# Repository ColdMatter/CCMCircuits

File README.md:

CCMCircuits
===========

This is a repository for circuits used by the Centre for Cold Matter at Imperial College. Each project should be in its own directory, and should contain a .brd and a .sch file, a "readme.md" file which gives any useful information on the circuit. You can also upload files used to make the circuit in the PCB mill, and any measurements that you make of the circuit's behaviour. Please try not to upload all of the temporary files made by Eagle.

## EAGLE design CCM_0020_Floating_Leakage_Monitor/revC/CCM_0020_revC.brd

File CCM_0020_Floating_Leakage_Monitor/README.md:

# CCM_0020 50kV Floating pA Leakage Current Monitor
     
This is a circuit used to monitor pA-level leakage currents on the HV plates of 
the ultracold edm experiment.  We have a design goal of having the leakage currents be less than 25 pA.  To make sure this is the case, we want to be able to measure currents at the pA level.  This is hard.  Floating the entire circuit up to a few tens of kV makes it even harder.  This is my kind of problem -NF.    

## Design Resources
- Bob Pease: What's all this teflon stuff anyhow?
- Bob Pease: What's all this femtoampere stuff anyhow?
- Keithley low-level measurement handbook
- LM662 datasheet
- Analog Devices ADA4530-1 datasheet: https://www.analog.com/media/en/technical-documentation/data-sheets/ADA4530-1.pdf 
- Analog Devices ADA4530-1 demo board user's guide: https://www.analog.com/media/en/technical-documentation/user-guides/ADA4530-1R-EBZ_UG-865.pdf

## Design Notes
The transmitter section of the circuit features three critical design elements: 
ultra low input leakage currents, ultra low power consumption, and high voltage 
isolation.  The former is required of any circuit capable of measuring currents 
on the pA level.  The most sensitive way to measure extremely low currents (like the fA-level features by some of the op amps we'll be using here) is to integrate for many seconds and read off the voltage.  Of course, you need an integrating capacitor with low leakage too: a length of teflon coated coaxial wire is a good choice, you can even drive the coax outer conductor with a shielding potential ("self shielded") to avoid dielectric relaxation effects.  The small enclosed volume also lowers the sensitivity to cosmic rays, to which you are sensitive to at this level.  To monitor the leakage on the edm electric field plates, we need a time-resolved signal, so integrating is out.  We don't care at the fA level, so this shouldn't pose a problem.  A sense resistor + buffer amplifier (alternatively, a transimpedance amplifier) should be sensitive enough and give us real-time measurements. 

Achieving ultra low input leakage currents starts with choosing an appropriate 
operational amplifier, in this case in a voltage "buffer" configuration.  Luckily, there are a number of (CMOS) op amps on the market that feature input leakage currents on the order of 10 fA.  We have the additional challenge of needing an op amp that has low quiescent current requirements.  The LMP2231 made by Texas Instruments seems to fit the bill: 20 fA input leakage current (typical, 1 pA max) while only needing 10 uA of quiescent current.

Taking advantage of the ultra-low input current leakage specification of our chosen op amp requires a significant amount of layout/design work.  It won't do us any good to use such an op amp on a dirty FR4 board that will leak currents of many pA into our inputs every time the humidity changes.  The first line of defense is to use a low-leakage circuit board material.  A 4-layer board with outer layers made of Rogers 4350B (a ceramic) and the inner substrate made of FR408 (for strength) seems like a good way to go.  Beyond that, high-impedance circuit inputs are shielded at numerous levels.  The buffer op amp inputs use a "guard ring" driven by a low impedance source (the op amp output) held at the same voltage as the inputs themselves, which eliminates leakage from surrounding on-board potentials.  The guard ring is exposed copper so that no charge carriers can leak past on the soldermask or silkscreen layers.  The guard ring extends underneath the top ceramic layer to shield the input pins (from below) from the FR4 inner layer.  A via fence on the outer perimeter of the guard ring completes the board-level shielding.  Additional shielding is achieved by two layers of brass boxes, the inner one (top and bottom of the board) at the same potential as the guard ring and the outer one (again, on both top and bottom) at floating "ground".  A triax cable uses the same two shielding potentials to bring the HV line into the circuit.

Of all the challenges to overcome here, the HV isolation is perhaps the easiest to overcome.  Optek makes the OPI15X series of opto-couplers/isolators that are rated to 50 kV in air.  We could just do our usual trick: use a sense resistor and buffer amplifier to generate a voltage, convert that voltage to a frequency using a VtoF converter and optically transmit that frequency.  Optical transmission can either be done using a fiber (e.g. Agilent's HFBR-1520) or an Optek OPI155 optoisolator.  However, both of these require significant (many mA) led drive current in order to toggle the logic output on the receiver.  Instead, I'm planning to use the OPI150 optocoupler (transmitting LED + receiving phototransistor) with the phototransistor receiver wired as a photodiode (base shorted to emitter) and the generated photocurrent being detected by a high-gain transimpedance amplifier.  In principle, this should allow us to get the signal out using much less power.  The output of the transimpedance could even feed into a precisely tuned comparator to give high sensitivity and logic-level outputs.  We could even transmit an analog signal instead of a digital one using the same setup but without the receiver comparator.  I think the digital approach will have better noise immunity, larger dynamic range, and potentially uses less power.  That means we'll likely have to do VtoF after all.  Even though you can't buy low power VtoF ICs (or VCOs), you can build your own.  The LTC1541 [op amp + comparator + voltage reference] has one option in the applications section of its datasheet.  You can build a 0-10 kHz VtoF with quiescent current requirements around 5 uA, some 200 x less than the lowest power monolithic solution.  

Along with the problem of high-voltage isolation comes the question of how to power the isolated transmitter section of the circuit.  The most obvious answer is to use batteries, but in practice that turns out to be relatively annoying.  An alternative is to power the circuit using some high-power leds and a solar panel on the transmitter.  This sounds elegant, and I think it probably could be if the transmitter was designed for very low-power operation, but in practice it makes the current monitors very big (and bright -- you need lots of optical power).  I've decided to try something crazy: design for ultra-low power on the transmitter and power it via photocurrent generated from (many of)
the same model of optocoupler that we're using to get the signal out.  With a max allowed LED current of 50 mA and a transfer ratio of ~2000:1, with six optocouplers I think I should be able to create a 2.5 V, 50 uA power supply on the transmitter circuit.  With a careful design I think that should be enough. 

## Known Issues

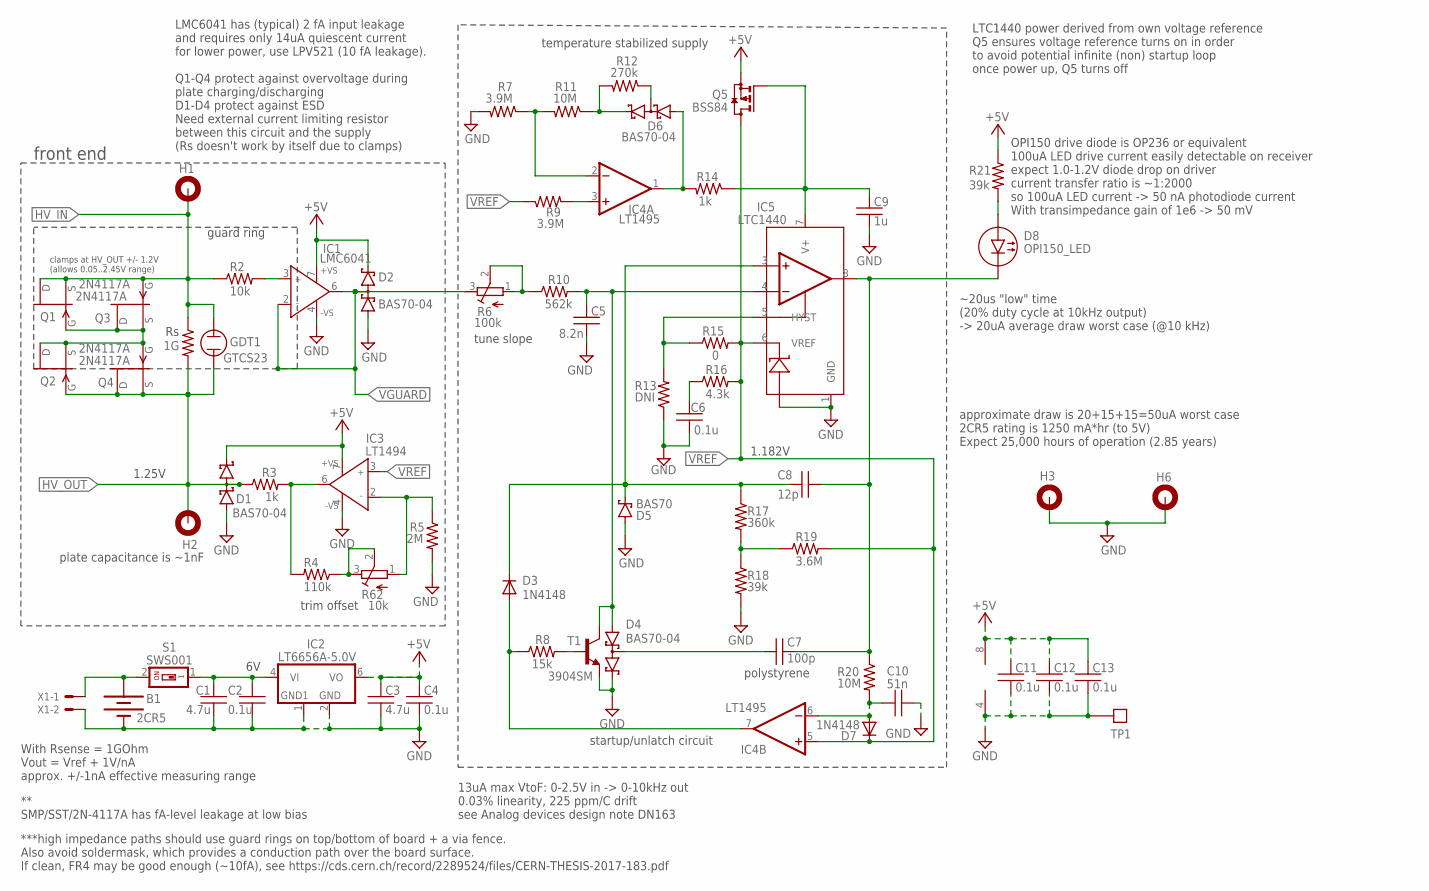
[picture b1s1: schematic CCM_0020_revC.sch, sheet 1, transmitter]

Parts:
B1: 2CR5
C1, C3: 4.7u; 0603
C2, C4, C6, C11, C12, C13: 0.1u; 0603
C5: 8.2n; 0603
C7: 100p; 0603
C8: 12p; 0603
C9: 1u; 0603
C10: 51n; 0603
D1, D2, D4, D6: BAS70-04; SOT23
D3, D7: 1N4148; SOD323_ST
D5: BAS70; SOD323_ST
D8: OPI150_LED
GDT1: GTCS23
H1, H2, H3, H6: MOUNT-PAD-ROUND3.0; 3,0-PAD
IC1: LMC6041; SO8
IC2: LT6656A-5.0V; SOT23-6
IC3: LT1494; SO8
IC4: LT1495; SO8
IC5: LTC1440; SO8
Q1, Q2, Q3, Q4: 2N4117A; SOT23
Q5: BSS84; SOT23
R1: 1G; 2512
R2: 10k; 0603
R3, R14: 1k; 0603
R4: 110k; 0603
R5: 2M; 0603
R6: 100k; RTRIM3224W
R7, R9: 3.9M; 0603
R8: 15k; 0603
R10: 562k; 0603
R11, R20: 10M; 0603
R12: 270k; 0603
R13: DNI; 0603
R15: 0; 0603
R16: 4.3k; 0603
R17: 360k; 0603
R18, R21: 39k; 0603
R19: 3.6M; 0603
R62: 10k; RTRIM3224W
S1: SWS001; SMS-001
T1: 3904SM; SOT23
TP1: TESTPOINT
X1: 22-23-2021

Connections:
+5V: C3.1, C4.1, C11.1, C12.1, C13.1, D1.2 (C2), D2.2 (C2), IC1.7 (+VS), IC2.6 (VO), IC3.7 (+VS), IC4.8 (V+), Q5.2 (S), R21.1
GND: B1.V- (-), C1.2, C2.2, C3.2, C4.2, C5.2, C6.1, C9.2, C10.2, C11.2, C12.2, C13.2, D1.1 (A1), D2.1 (A1), D4.2 (C2), D5.A, H3.B3,0, H6.B3,0, IC1.4 (-VS), IC2.1 (GND1), IC2.2 (GND), IC3.4 (-VS), IC4.4 (V-), IC5.1 (GND), IC5.2 (V-), R5.2, R7.2, R13.1, R18.2, T1.2 (E), TP1.P$1, X1.2
HV_IN: GDT1.P$1 (1), H1.B3,0, Q1.1 (D), Q1.2 (S), Q3.3 (G), R1.1, R2.1
HV_IN1: Q1.3 (G), Q2.1 (D), Q2.2 (S), Q3.1 (D), Q3.2 (S), Q4.3 (G)
HV_OUT: D1.3 (C1A2), GDT1.P$2 (2), H2.B3,0, Q2.3 (G), Q4.1 (D), Q4.2 (S), R1.2, R3.1
HYST: IC5.5 (HYST), R13.2, R15.1
unnamed: C9.1, IC5.7 (V+), Q5.1 (G), R14.1
unnamed: D8.P$1 (1(A)), R21.2
unnamed: R6.1 (A), R6.2 (S), R10.1
unnamed: IC1.3 (IN+), R2.2
unnamed: C6.2, R16.1
unnamed: C5.1, D4.1 (A1), IC5.4 (-IN), R10.2, T1.3 (C)
unnamed: C7.1, D4.3 (C1A2)
unnamed: R8.2, T1.1 (B)
unnamed: D3.A, IC4.7 (OUT), R8.1
unnamed: R17.2, R18.1, R19.1
unnamed: C8.1, D3.C, D5.C, IC5.3 (+IN), R17.1
unnamed: C10.1, D7.A, IC4.6 (-IN), R20.2
unnamed: D6.1 (A1), IC4.1 (OUT), R14.2
unnamed: D6.2 (C2), R11.1, R12.2
unnamed: IC4.2 (-IN), R7.1, R11.2
unnamed: C1.1, C2.1, IC2.4 (VI), S1.1
unnamed: D6.3 (C1A2), R12.1
unnamed: IC4.3 (+IN), R9.2
unnamed: IC3.2 (IN-), R5.1, R62.1 (A)
unnamed: IC3.6 (OUT), R3.2, R4.2
unnamed: R4.1, R62.2 (S), R62.3 (E)
unnamed: B1.V+ (+), S1.2, X1.1
VGUARD: D2.3 (C1A2), IC1.2 (IN-), IC1.6 (OUT), R6.3 (E)
VREF: D7.C, IC3.3 (IN+), IC4.5 (+IN), IC5.6 (VREF), Q5.3 (D), R9.1, R15.2, R16.2, R19.2
VTOF_OUTPUT: C7.2, C8.2, D8.P$2 (2(C)), IC5.8 (OUT), R20.1

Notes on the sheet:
** SMP/SST/2N-4117A has fA-level leakage at low bias
plate capacitance is ~1nF
With Rsense = 1GOhm Vout = Vref + 1V/nA approx. +/-1nA effective measuring range
***high impedance paths should use guard rings on top/bottom of board + a via fence. Also avoid soldermask, which provides a conduction path over the board surface. If clean, FR4 may be good enough (~10fA), see https://cds.cern.ch/record/2289524/files/CERN-THESIS-2017-183.pdf
polystyrene
front end
13uA max VtoF: 0-2.5V in -> 0-10kHz out 0.03% linearity, 225 ppm/C drift see Analog devices design note DN163
1.182V
clamps at HV_OUT +/- 1.2V (allows 0.05..2.45V range)
approximate draw is 20+15+15=50uA worst case 2CR5 rating is 1250 mA*hr (to 5V) Expect 25,000 hours of operation (2.85 years)
guard ring
~20us "low" time (20% duty cycle at 10kHz output) -> 20uA average draw worst case (@10 kHz)
OPI150 drive diode is OP236 or equivalent 100uA LED drive current easily detectable on receiver expect 1.0-1.2V diode drop on driver current transfer ratio is ~1:2000 so 100uA LED current -> 50 nA photodiode current With transimpedance gain of 1e6 -> 50 mV
LMC6041 has (typical) 2 fA input leakage and requires only 14uA quiescent current for lower power, use LPV521 (10 fA leakage). Q1-Q4 protect against overvoltage during plate charging/discharging D1-D4 protect against ESD Need external current limiting resistor between this circuit and the supply (R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
temperature stabilized supply
startup/unlatch circuit
tune slope
1.25V
LTC1440 power derived from own voltage reference Q5 ensures voltage reference turns on in order to avoid potential infinite (non) startup loop once power up, Q5 turns off
trim offset

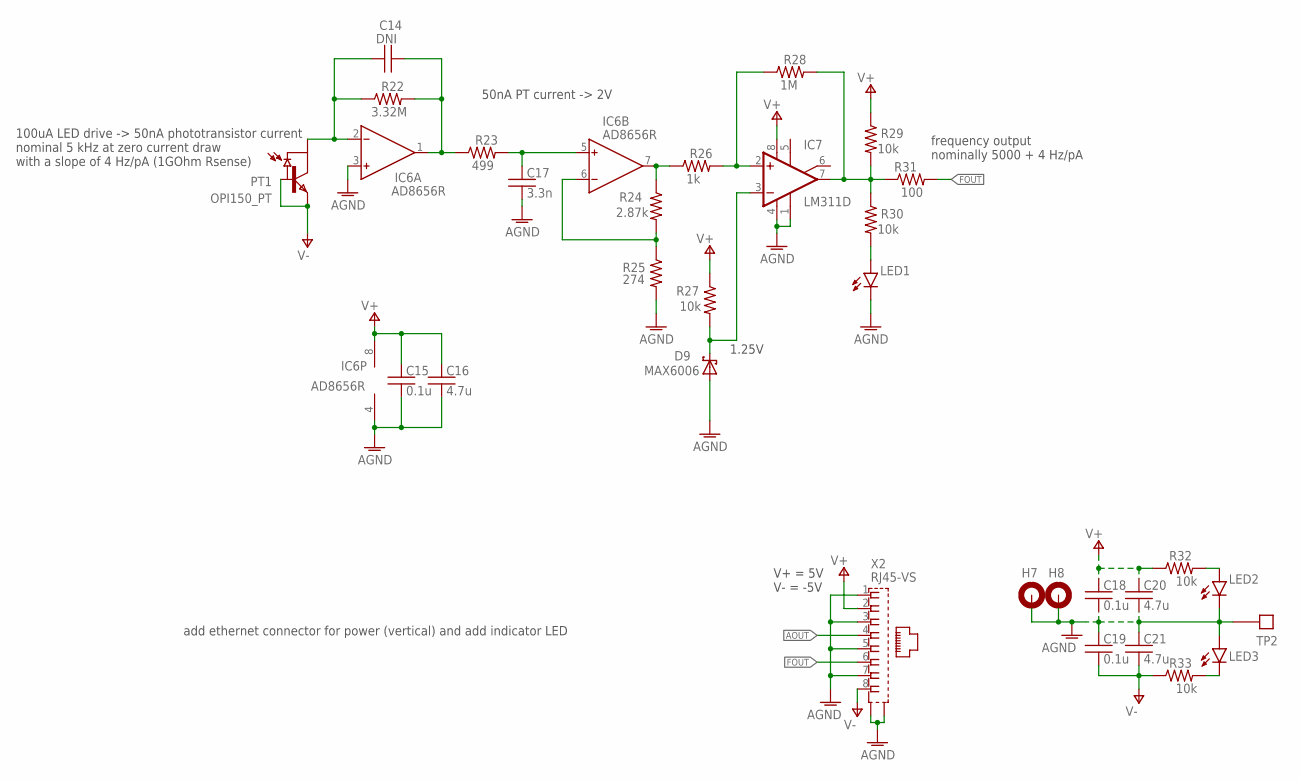
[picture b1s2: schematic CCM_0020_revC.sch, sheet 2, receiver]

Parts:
C14: DNI; 0603
C15, C18, C19: 0.1u; 0603
C16, C20, C21: 4.7u; 0603
C17: 3.3n; 0603
D9: MAX6006; SOT23
H7, H8: MOUNT-PAD-ROUND3.0; 3,0-PAD
IC6: AD8656R; SO8
IC7: LM311D; SO08
LED1, LED2, LED3: LEDCHIP-LED0603; CHIP-LED0603
PT1: OPI150_PT; OPI150_PHOTOTRANSISTOR
R22: 3.32M; 0603
R23: 499; 0603
R24: 2.87k; 0603
R25: 274; 0603
R26: 1k; 0603
R27, R29, R30, R32, R33: 10k; 0603
R28: 1M; 0603
R31: 100; 0603
TP2: TESTPOINT
X2: RJ45-VS

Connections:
AGND: C15.2, C16.2, C17.2, C18.2, C19.1, C20.2, C21.1, D9.2 (A), H7.B3,0, H8.B3,0, IC6.3 (IN+), IC6.4 (V-), IC7.1 (GND), IC7.4 (V-), LED1.C, LED2.C, LED3.A, R25.2, TP2.P$1, X2.1, X2.3, X2.5, X2.7, X2.S1, X2.S2; also elsewhere on the board
AOUT: X2.4; also elsewhere on the board
FOUT: R31.2, X2.6; also elsewhere on the board
unnamed: LED2.A, R32.2
unnamed: C14.1, IC6.2 (IN-), PT1.P3 (COLLECTOR), R22.1
unnamed: C14.2, IC6.1 (OUT), R22.2, R23.1
unnamed: C17.1, IC6.5 (IN+), R23.2
unnamed: IC6.6 (IN-), R24.2, R25.1
unnamed: IC6.7 (OUT), R24.1, R26.1
unnamed: IC7.2 (+IN), R26.2, R28.1
unnamed: D9.1 (C), IC7.3 (-IN), R27.2
unnamed: LED3.C, R33.2
unnamed: LED1.A, R30.2
unnamed: IC7.7 (OUT), R28.2, R29.2, R30.1, R31.1
V+: C15.1, C16.1, C18.1, C20.1, IC6.8 (V+), IC7.8 (V+), R27.1, R29.1, R32.1, X2.2; also elsewhere on the board
V-: C19.2, C21.2, PT1.P4 (BASE), PT1.P5 (EMITTER), R33.1, X2.8; also elsewhere on the board

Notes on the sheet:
100uA LED drive -> 50nA phototransistor current nominal 5 kHz at zero current draw with a slope of 4 Hz/pA (1GOhm Rsense)
50nA PT current -> 2V
1.25V
frequency output nominally 5000 + 4 Hz/pA
V+ = 5V V- = -5V
add ethernet connector for power (vertical) and add indicator LED

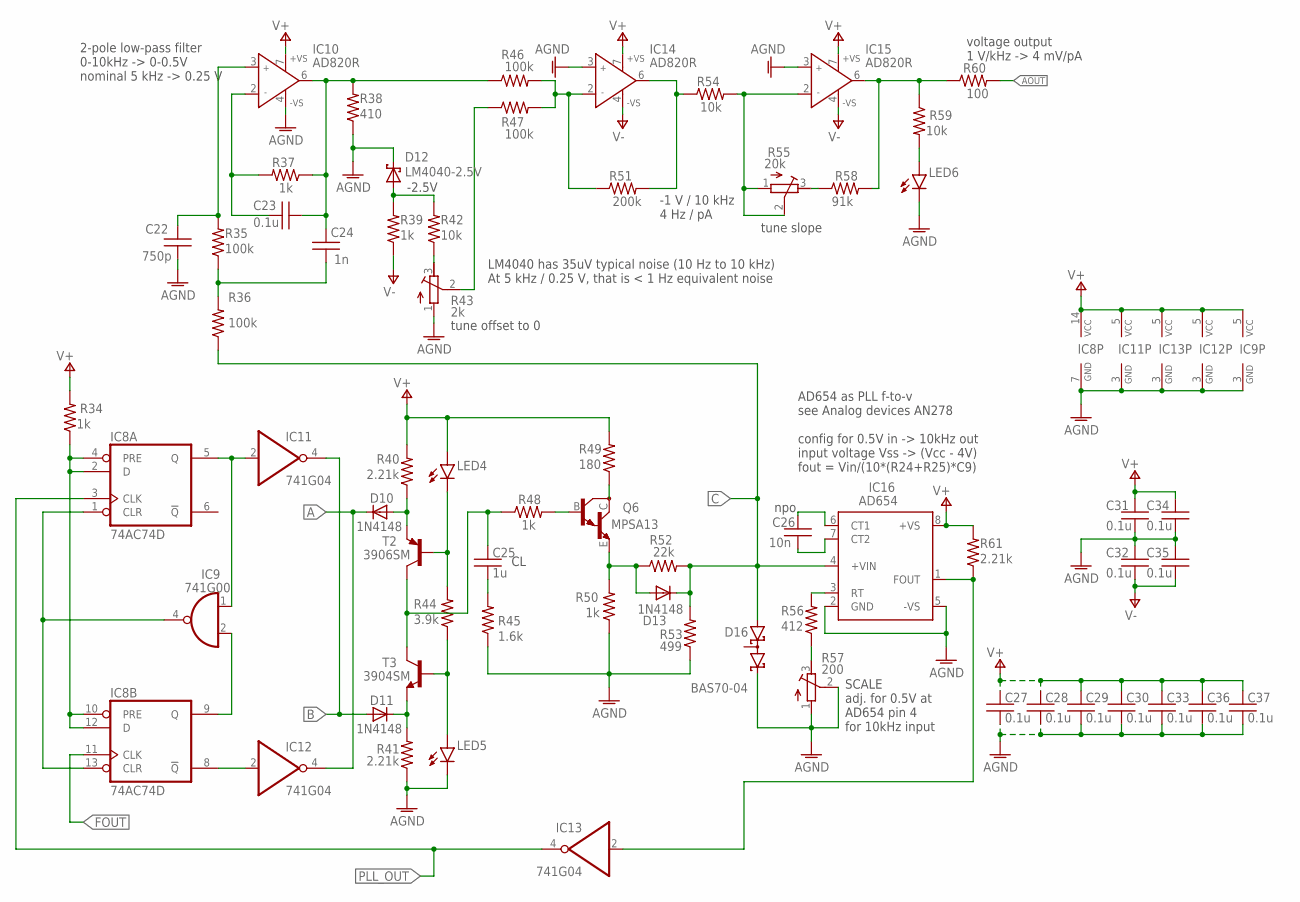
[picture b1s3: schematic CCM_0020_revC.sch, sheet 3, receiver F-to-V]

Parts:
C22: 750p; 0603
C23, C27, C28, C29, C30, C31, C32, C33, C34, C35, C36, C37: 0.1u; 0603
C24: 1n; 0603
C25: 1u; 0603
C26: 10n; 0603
D10, D11, D13: 1N4148; SOD323_ST
D12: LM4040-2.5V; SOT23
D16: BAS70-04; SOT23
IC8: 74AC74D; SO14
IC9: 741G00; SOT23-5
IC10, IC14, IC15: AD820R; SO8
IC11, IC12, IC13: 741G04; SOT23-5
IC16: AD654; SO08
LED4, LED5, LED6: LEDCHIP-LED0603; CHIP-LED0603
Q6: MPSA13; SOT23-BEC
R34, R37, R39, R48, R50: 1k; 0603
R35, R36, R46, R47: 100k; 0603
R38: 410; 0603
R40, R41, R61: 2.21k; 0603
R42, R54, R59: 10k; 0603
R43: 2k; RTRIM3224W
R44: 3.9k; 0603
R45: 1.6k; 0603
R49: 180; 0603
R51: 200k; 0603
R52: 22k; 0603
R53: 499; 0603
R55: 20k; RTRIM3224W
R56: 412; 0603
R57: 200; RTRIM3224W
R58: 91k; 0603
R60: 100; 0603
T2: 3906SM; SOT23-BEC
T3: 3904SM; SOT23

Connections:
A: D10.C, IC12.4 (O)
AGND: C22.1, C27.2, C28.2, C29.2, C30.2, C31.1, C32.2, C33.2, C34.1, C35.2, C36.2, C37.2, D12.1 (C), D16.2 (C2), IC8.7 (GND), IC9.3 (GND), IC10.4 (-VS), IC11.3 (GND), IC12.3 (GND), IC13.3 (GND), IC14.3 (IN+), IC15.3 (IN+), IC16.2 (GND), IC16.5 (-VS), LED5.C, LED6.C, R38.1, R41.1, R43.1 (A), R45.1, R50.1, R53.1, R57.1 (A), R57.2 (S); also elsewhere on the board
AOUT: R60.2; also elsewhere on the board
B: D11.A, IC11.4 (O)
C: D13.C, D16.1 (A1), IC16.4 (+VIN), R36.1, R52.2, R53.2
FOUT: IC8.11 (CLK); also elsewhere on the board
unnamed: IC8.1 (CLR), IC8.13 (CLR), IC9.4 (O)
unnamed: IC8.9 (Q), IC9.2 (I1)
unnamed: IC8.8 (!Q), IC12.2 (I)
unnamed: IC8.5 (Q), IC9.1 (I0), IC11.2 (I)
unnamed: R56.1, R57.3 (E)
unnamed: C25.1, R48.1, T2.C, T3.3 (C)
unnamed: D11.C, R41.2, T3.2 (E)
unnamed: LED4.C, R44.2, T2.B
unnamed: LED5.A, R44.1, T3.1 (B)
unnamed: C25.2, R45.2
unnamed: Q6.C, R49.1
unnamed: Q6.B, R48.2
unnamed: D13.A, Q6.E, R50.2, R52.1
unnamed: IC16.3 (RT), R56.2
unnamed: C26.1, IC16.6 (CT1)
unnamed: C26.2, IC16.7 (CT2)
unnamed: IC13.2 (I), IC16.1 (FOUT), R61.1
unnamed: C24.1, R35.1, R36.2
unnamed: C22.2, IC10.3 (IN+), R35.2
unnamed: C23.2, C24.2, IC10.6 (OUT), R37.1, R38.2, R46.1
unnamed: C23.1, IC10.2 (IN-), R37.2
unnamed: IC14.2 (IN-), R46.2, R47.2, R51.1
unnamed: IC15.2 (IN-), R54.2, R55.1 (A), R55.2 (S)
unnamed: IC15.6 (OUT), R58.2, R59.1, R60.1
unnamed: IC14.6 (OUT), R51.2, R54.1
unnamed: D12.2 (A), R39.2, R42.2
unnamed: R43.2 (S), R47.1
unnamed: R42.1, R43.3 (E)
unnamed: R55.3 (E), R58.1
unnamed: D10.A, R40.1, T2.E
unnamed: LED6.A, R59.2
unnamed: IC8.2 (D), IC8.4 (PRE), IC8.10 (PRE), IC8.12 (D), R34.1
PLL_OUT: IC8.3 (CLK), IC13.4 (O)
V+: C27.1, C28.1, C29.1, C30.1, C31.2, C33.1, C34.2, C36.1, C37.1, IC8.14 (VCC), IC9.5 (VCC), IC10.7 (+VS), IC11.5 (VCC), IC12.5 (VCC), IC13.5 (VCC), IC14.7 (+VS), IC15.7 (+VS), IC16.8 (+VS), LED4.A, R34.2, R40.2, R49.2, R61.2; also elsewhere on the board
V-: C32.1, C35.1, IC14.4 (-VS), IC15.4 (-VS), R39.1; also elsewhere on the board

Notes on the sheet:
npo
SCALE adj. for 0.5V at AD654 pin 4 for 10kHz input
2-pole low-pass filter 0-10kHz -> 0-0.5V nominal 5 kHz -> 0.25 V
AD654 as PLL f-to-v see Analog devices AN278 config for 0.5V in -> 10kHz out input voltage Vss -> (Vcc - 4V) fout = Vin/(10*(R24+R25)*C9)
-2.5V
tune offset to 0
-1 V / 10 kHz 4 Hz / pA
voltage output 1 V/kHz -> 4 mV/pA
tune slope
LM4040 has 35uV typical noise (10 Hz to 10 kHz) At 5 kHz / 0.25 V, that is < 1 Hz equivalent noise

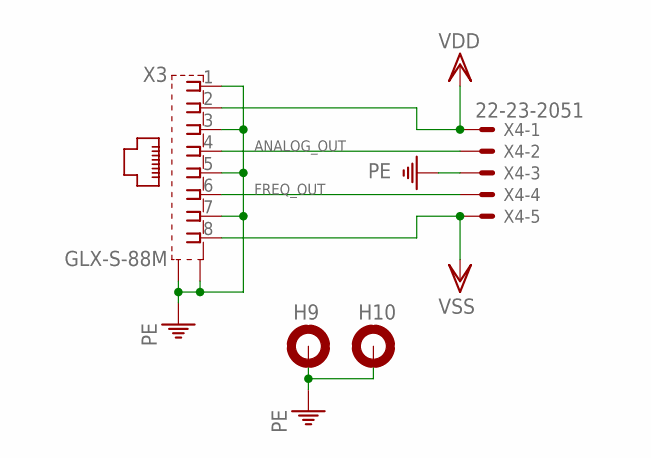
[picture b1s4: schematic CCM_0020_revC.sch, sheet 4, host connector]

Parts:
H9, H10: MOUNT-PAD-ROUND3.0; 3,0-PAD
X3: GLX-S-88M
X4: 22-23-2051

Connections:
ANALOG_OUT: X3.4, X4.2
FREQ_OUT: X3.6, X4.4
PE: H9.B3,0, H10.B3,0, X3.1, X3.3, X3.5, X3.7, X3.S1, X3.S2, X4.3
VDD: X3.2, X4.1
VSS: X3.8, X4.5

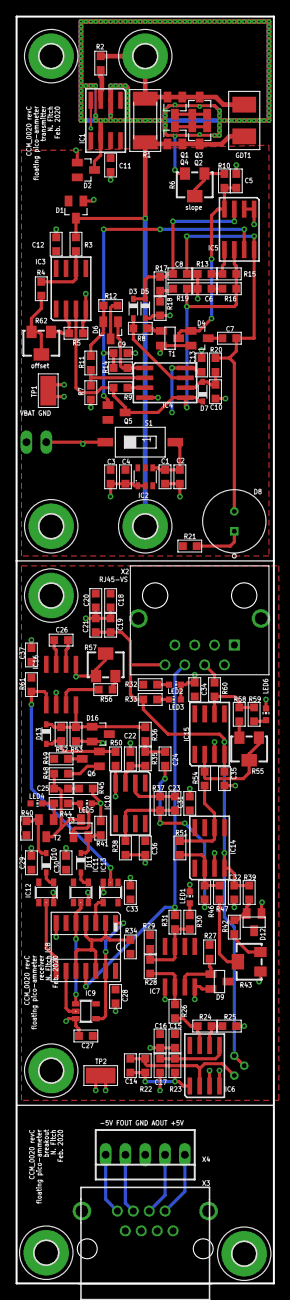
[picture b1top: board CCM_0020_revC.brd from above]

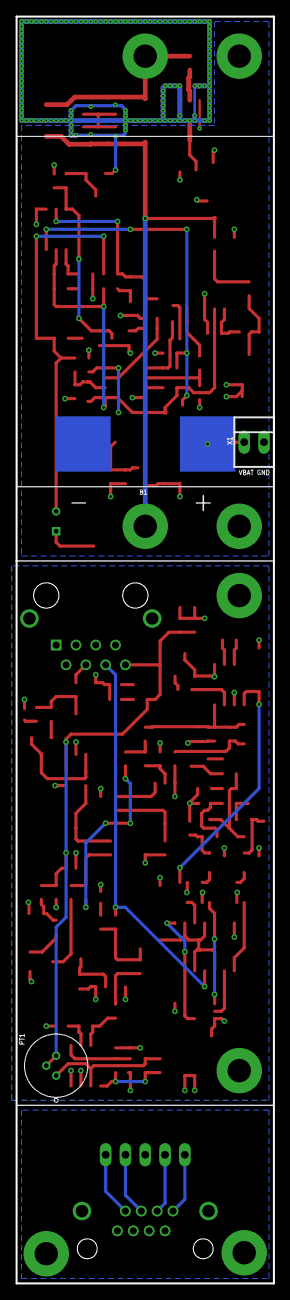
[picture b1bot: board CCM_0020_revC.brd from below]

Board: 2 copper layers, 33.0 x 162.6 mm, 162 parts (3 on the bottom side), 88 nets.

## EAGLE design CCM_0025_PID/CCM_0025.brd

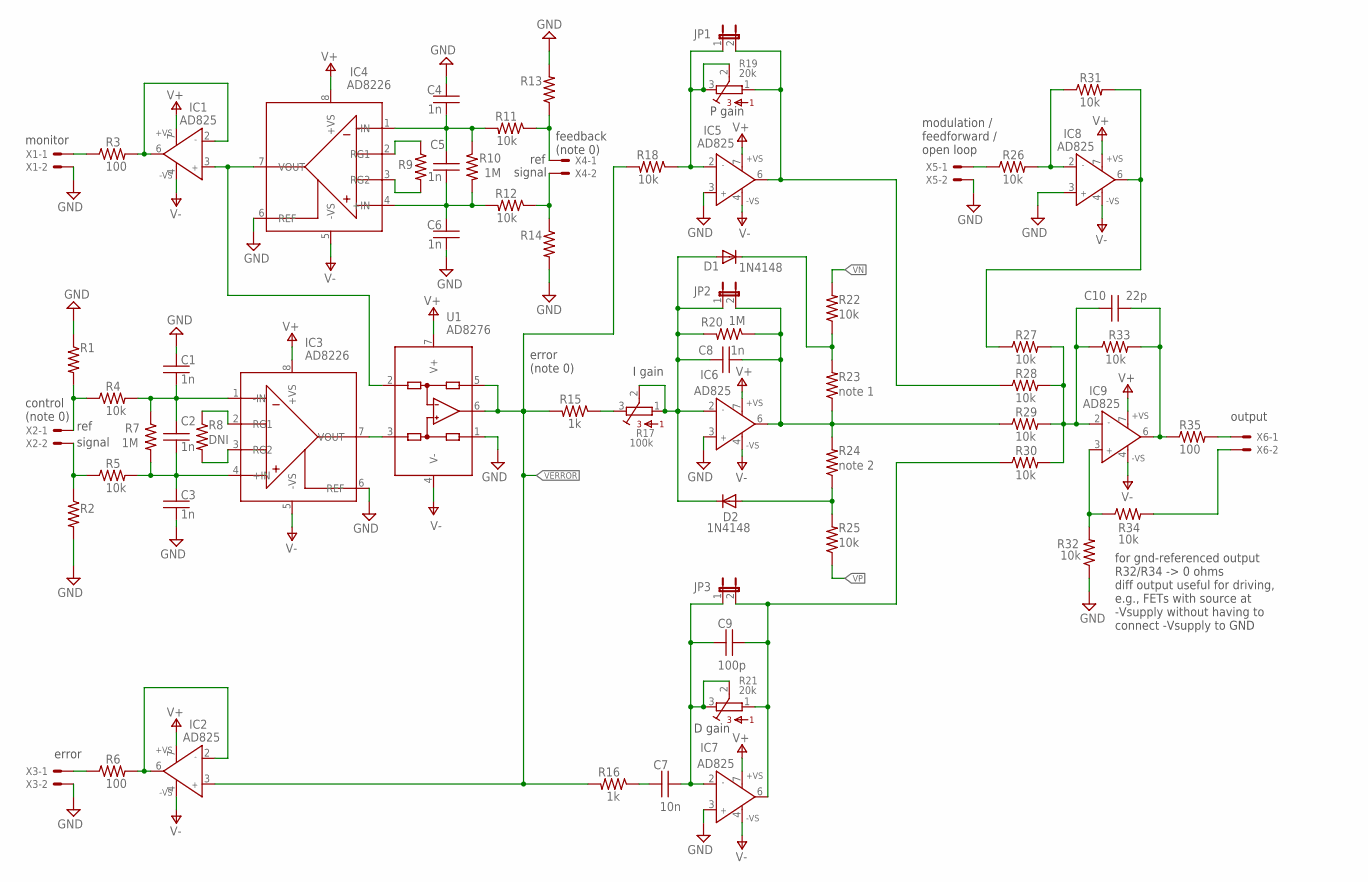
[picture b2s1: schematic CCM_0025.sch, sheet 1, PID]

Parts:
C1, C2, C3, C4, C5, C6, C8: 1n; 0603
C7: 10n; 0603
C9: 100p; 0603
C10: 22p; 0603
D1, D2: 1N4148; SOD323_ST
IC1, IC2, IC5, IC6, IC7, IC8, IC9: AD825; SO8
IC3, IC4: AD8226; SO08
JP1, JP2, JP3: JP1E; JP1
R1, R2, R4, R5, R11, R12, R13, R14, R18, R22, R25, R26, R27, R28, R29, R30, R31, R32, R33, R34: 10k; 0603
R3, R6, R35: 100; 0603
R7, R10, R20: 1M; 0603
R8, R9: DNI; 0603
R15, R16: 1k; 0603
R17: 100k; 3386C
R19, R21: 20k; 3386C
R23: note 1; 0603
R24: note 2; 0603
U1: AD8276; SO8
X1, X2, X3, X4, X5, X6: 22-23-2021

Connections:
GND: C1.1, C3.2, C4.1, C6.2, IC3.6 (REF), IC4.6 (REF), IC5.3 (IN+), IC6.3 (IN+), IC7.3 (IN+), IC8.3 (IN+), R1.1, R2.2, R13.2, R14.2, R32.1, U1.1 (REF), X1.2, X3.2, X5.2; also elsewhere on the board
unnamed: R2.1, R5.1, X2.2
unnamed: R1.2, R4.1, X2.1
unnamed: C7.1, C9.2, IC7.2 (IN-), JP3.1, R21.2, R21.3
unnamed: IC3.2 (RG1), R8.1
unnamed: C1.2, C2.1, IC3.1 (-IN), R4.2, R7.1
unnamed: C2.2, C3.1, IC3.4 (+IN), R5.2, R7.2
unnamed: R3.1, X1.1
unnamed: IC3.3 (RG2), R8.2
unnamed: IC1.2 (IN-), IC1.6 (OUT), R3.2
unnamed: R26.1, X5.1
unnamed: C9.1, IC7.6 (OUT), JP3.2, R21.1, R30.1
unnamed: C7.2, R16.1
unnamed: R34.2, X6.2
unnamed: C10.2, IC9.2 (IN-), R27.2, R28.2, R29.2, R30.2, R33.1
unnamed: D1.C, R22.1, R23.2
unnamed: C10.1, IC9.6 (OUT), R33.2, R35.1
unnamed: IC9.3 (IN+), R32.2, R34.1
unnamed: R35.2, X6.1
unnamed: IC3.7 (VOUT), U1.3 (+IN)
unnamed: R12.1, R14.1, X4.2
unnamed: IC4.2 (RG1), R9.1
unnamed: IC4.3 (RG2), R9.2
unnamed: C4.2, C5.1, IC4.1 (-IN), R10.1, R11.2
unnamed: C5.2, C6.1, IC4.4 (+IN), R10.2, R12.2
unnamed: R11.1, R13.1, X4.1
unnamed: IC5.2 (IN-), JP1.1, R18.1, R19.2, R19.3
unnamed: IC5.6 (OUT), JP1.2, R19.1, R28.1
unnamed: R15.1, R17.3
unnamed: C8.2, D1.A, D2.C, IC6.2 (IN-), JP2.1, R17.1, R17.2, R20.2
unnamed: D2.A, R24.1, R25.2
unnamed: C8.1, IC6.6 (OUT), JP2.2, R20.1, R23.1, R24.2, R29.1
unnamed: IC1.3 (IN+), IC4.7 (VOUT), U1.2 (-IN)
unnamed: R6.1, X3.1
unnamed: IC2.2 (IN-), IC2.6 (OUT), R6.2
unnamed: IC8.2 (IN-), R26.2, R31.1
unnamed: IC8.6 (OUT), R27.1, R31.2
V+: IC1.7 (+VS), IC2.7 (+VS), IC3.8 (+VS), IC4.8 (+VS), IC5.7 (+VS), IC6.7 (+VS), IC7.7 (+VS), IC8.7 (+VS), IC9.7 (+VS), U1.7 (V+); also elsewhere on the board
V-: IC1.4 (-VS), IC2.4 (-VS), IC3.5 (-VS), IC4.5 (-VS), IC5.4 (-VS), IC6.4 (-VS), IC7.4 (-VS), IC8.4 (-VS), IC9.4 (-VS), U1.4 (V-); also elsewhere on the board
VERROR: IC2.3 (IN+), R15.2, R16.2, R18.2, U1.5 (SENSE), U1.6 (OUT)
VN: R22.2; also elsewhere on the board
VP: R25.1; also elsewhere on the board

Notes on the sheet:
control (note 0)
monitor
signal
ref
feedback (note 0)
error
P gain
I gain
D gain
modulation / feedforward / open loop
output
error (note 0)
for gnd-referenced output R32/R34 -> 0 ohms diff output useful for driving, e.g., FETs with source at -Vsupply without having to connect -Vsupply to GND

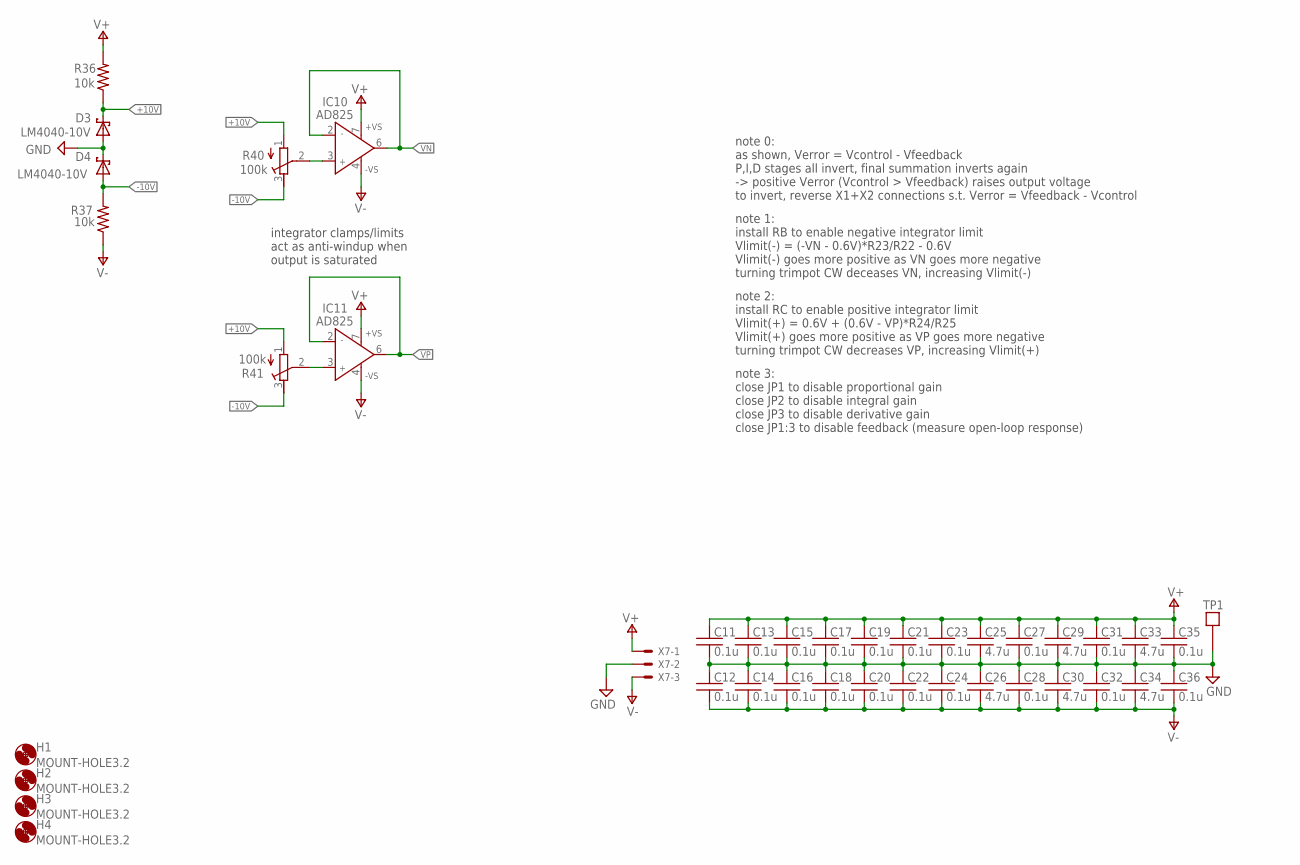
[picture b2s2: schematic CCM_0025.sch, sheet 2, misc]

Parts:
C11, C12, C13, C14, C15, C16, C17, C18, C19, C20, C21, C22, C23, C24, C27, C28, C31, C32, C35, C36: 0.1u; 0603
C25, C26, C29, C30, C33, C34: 4.7u; 0603
D3, D4: LM4040-10V; SOT23
H1, H2, H3, H4: MOUNT-HOLE3.2; 3,2
IC10, IC11: AD825; SO8
R36, R37: 10k; 0603
R40, R41: 100k; RTRIM3296W
TP1: TESTPOINT
X7: 22-23-2031

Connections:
+10V: D3.1 (C), R36.1, R40.1 (A), R41.1 (A)
-10V: D4.2 (A), R37.2, R40.3 (E), R41.3 (E)
GND: C11.2, C12.1, C13.2, C14.1, C15.2, C16.1, C17.2, C18.1, C19.2, C20.1, C21.2, C22.1, C23.2, C24.1, C25.2, C26.1, C27.2, C28.1, C29.2, C30.1, C31.2, C32.1, C33.2, C34.1, C35.2, C36.1, D3.2 (A), D4.1 (C), TP1.P$1, X7.2; also elsewhere on the board
unnamed: IC10.3 (IN+), R40.2 (S)
unnamed: IC11.3 (IN+), R41.2 (S)
V+: C11.1, C13.1, C15.1, C17.1, C19.1, C21.1, C23.1, C25.1, C27.1, C29.1, C31.1, C33.1, C35.1, IC10.7 (+VS), IC11.7 (+VS), R36.2, X7.1; also elsewhere on the board
V-: C12.2, C14.2, C16.2, C18.2, C20.2, C22.2, C24.2, C26.2, C28.2, C30.2, C32.2, C34.2, C36.2, IC10.4 (-VS), IC11.4 (-VS), R37.1, X7.3; also elsewhere on the board
VN: IC10.2 (IN-), IC10.6 (OUT); also elsewhere on the board
VP: IC11.2 (IN-), IC11.6 (OUT); also elsewhere on the board

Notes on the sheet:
integrator clamps/limits act as anti-windup when output is saturated
note 1: install RB to enable negative integrator limit Vlimit(-) = (-VN - 0.6V)*R23/R22 - 0.6V Vlimit(-) goes more positive as VN goes more negative turning trimpot CW deceases VN, increasing Vlimit(-)
note 2: install RC to enable positive integrator limit Vlimit(+) = 0.6V + (0.6V - VP)*R24/R25 Vlimit(+) goes more positive as VP goes more negative turning trimpot CW decreases VP, increasing Vlimit(+)
note 3: close JP1 to disable proportional gain close JP2 to disable integral gain close JP3 to disable derivative gain close JP1:3 to disable feedback (measure open-loop response)
note 0: as shown, Verror = Vcontrol - Vfeedback P,I,D stages all invert, final summation inverts again -> positive Verror (Vcontrol > Vfeedback) raises output voltage to invert, reverse X1+X2 connections s.t. Verror = Vfeedback - Vcontrol

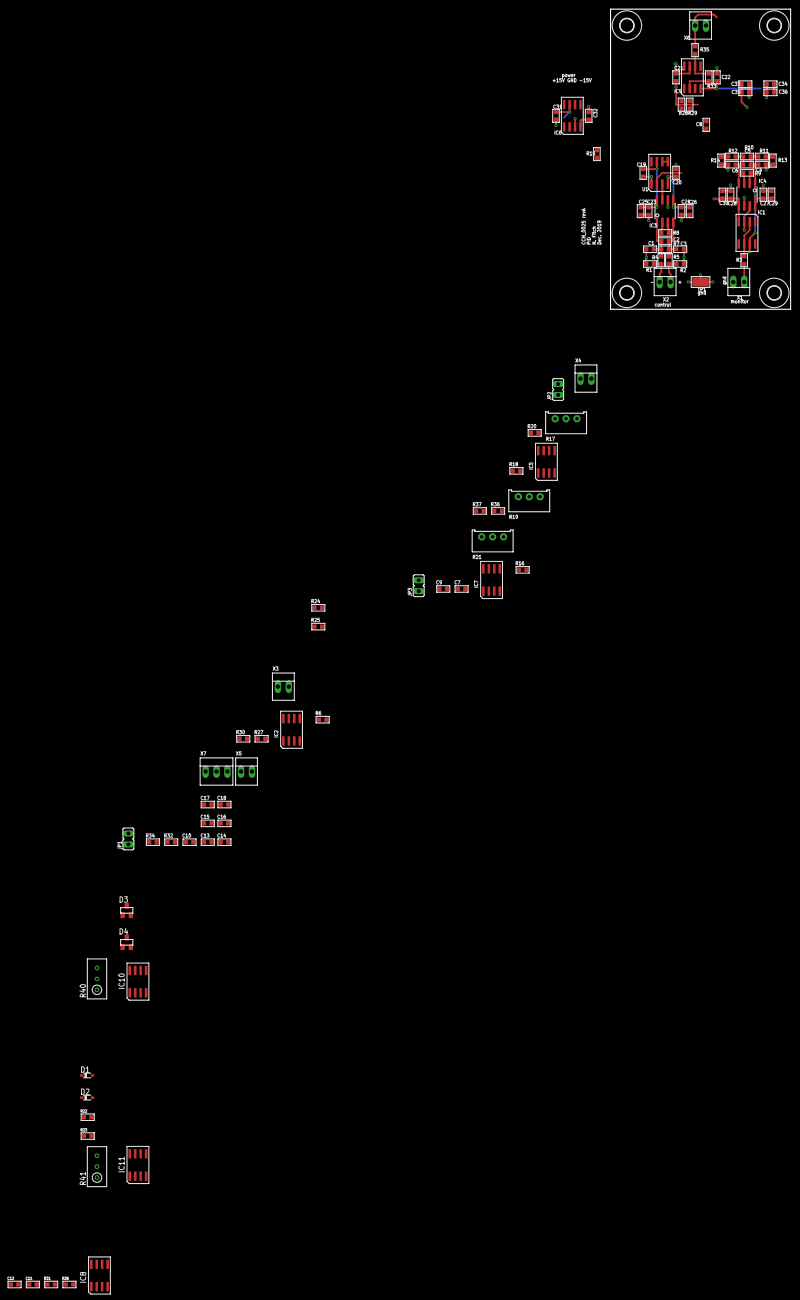
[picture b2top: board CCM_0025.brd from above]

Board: 2 copper layers, 41.9 x 69.8 mm, 106 parts (0 on the bottom side), 46 nets.

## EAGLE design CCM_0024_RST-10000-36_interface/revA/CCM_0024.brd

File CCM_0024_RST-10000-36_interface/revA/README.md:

# CCM 0024 RevA

This is an interface board for the rear-panel connection on the 10 kW Meanwell RST-10000-36 power supply that we are using for the CaF transport coils.

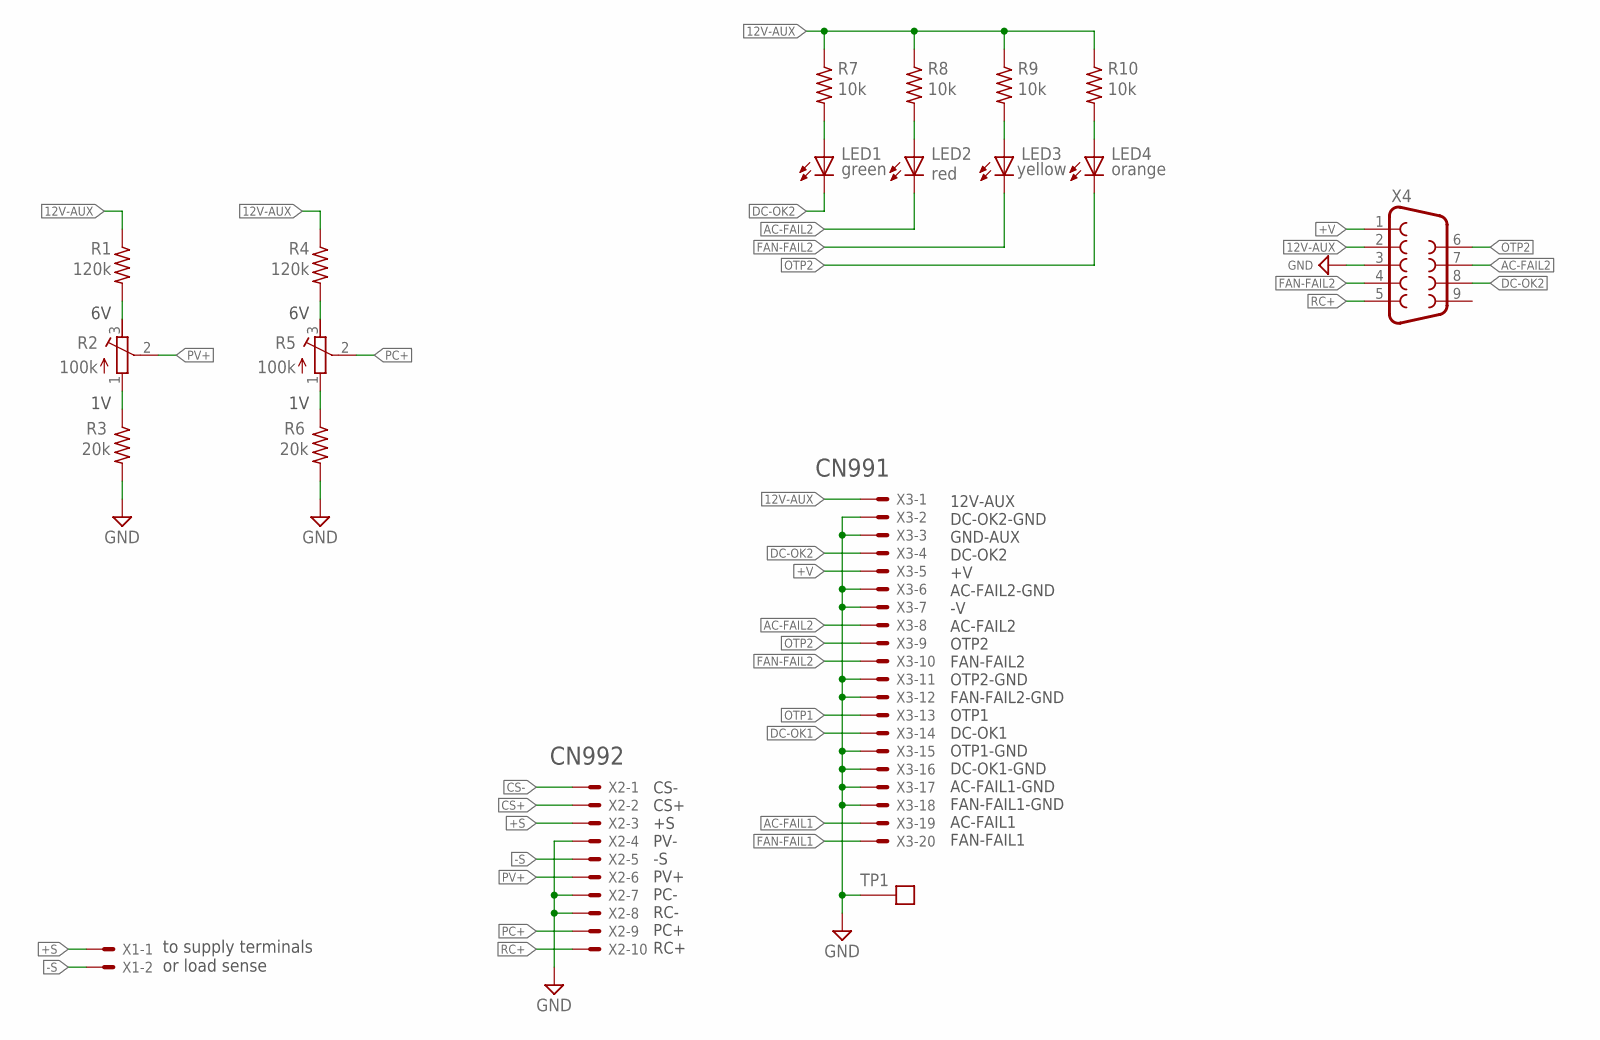
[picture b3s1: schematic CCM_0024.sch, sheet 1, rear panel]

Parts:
LED1: green; LED_SML0603
LED2: red; LED_SML0603
LED3: yellow; LED_SML0603
LED4: orange; LED_SML0603
R1, R4: 120k; 0603
R2, R5: 100k; RTRIM3296Y
R3, R6: 20k; 0603
R7, R8, R9, R10: 10k; 0603
TP1: TESTPOINT
X1: 22-23-2021
X2: 87758-1016
X3: 87758-2016
X4: F09V

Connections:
12V-AUX: R1.1, R4.1, R7.1, R8.1, R9.1, R10.1, X3.1, X4.2
+S: X1.1, X2.3
+V: X3.5, X4.1
-S: X1.2, X2.5
AC-FAIL1: X3.19
AC-FAIL2: LED2.C, X3.8, X4.7
CS+: X2.2
CS-: X2.1
DC-OK1: X3.14
DC-OK2: LED1.C, X3.4, X4.8
FAN-FAIL1: X3.20
FAN-FAIL2: LED3.C, X3.10, X4.4
GND: R3.2, R6.2, TP1.P$1, X2.4, X2.7, X2.8, X3.2, X3.3, X3.6, X3.7, X3.11, X3.12, X3.15, X3.16, X3.17, X3.18, X4.3
unnamed: LED1.A, R7.2
unnamed: R2.1 (A), R3.1
unnamed: R1.2, R2.3 (E)
unnamed: LED2.A, R8.2
unnamed: LED3.A, R9.2
unnamed: LED4.A, R10.2
unnamed: R5.1 (A), R6.1
unnamed: R4.2, R5.3 (E)
OTP1: X3.13
OTP2: LED4.C, X3.9, X4.6
PC+: R5.2 (S), X2.9
PV+: R2.2 (S), X2.6
RC+: X2.10, X4.5

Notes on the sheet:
CN991
CN992
CS- CS+ +S PV- -S PV+ PC- RC- PC+ RC+
12V-AUX DC-OK2-GND GND-AUX DC-OK2 +V AC-FAIL2-GND -V AC-FAIL2 OTP2 FAN-FAIL2 OTP2-GND FAN-FAIL2-GND OTP1 DC-OK1 OTP1-GND DC-OK1-GND AC-FAIL1-GND FAN-FAIL1-GND AC-FAIL1 FAN-FAIL1
to supply terminals or load sense

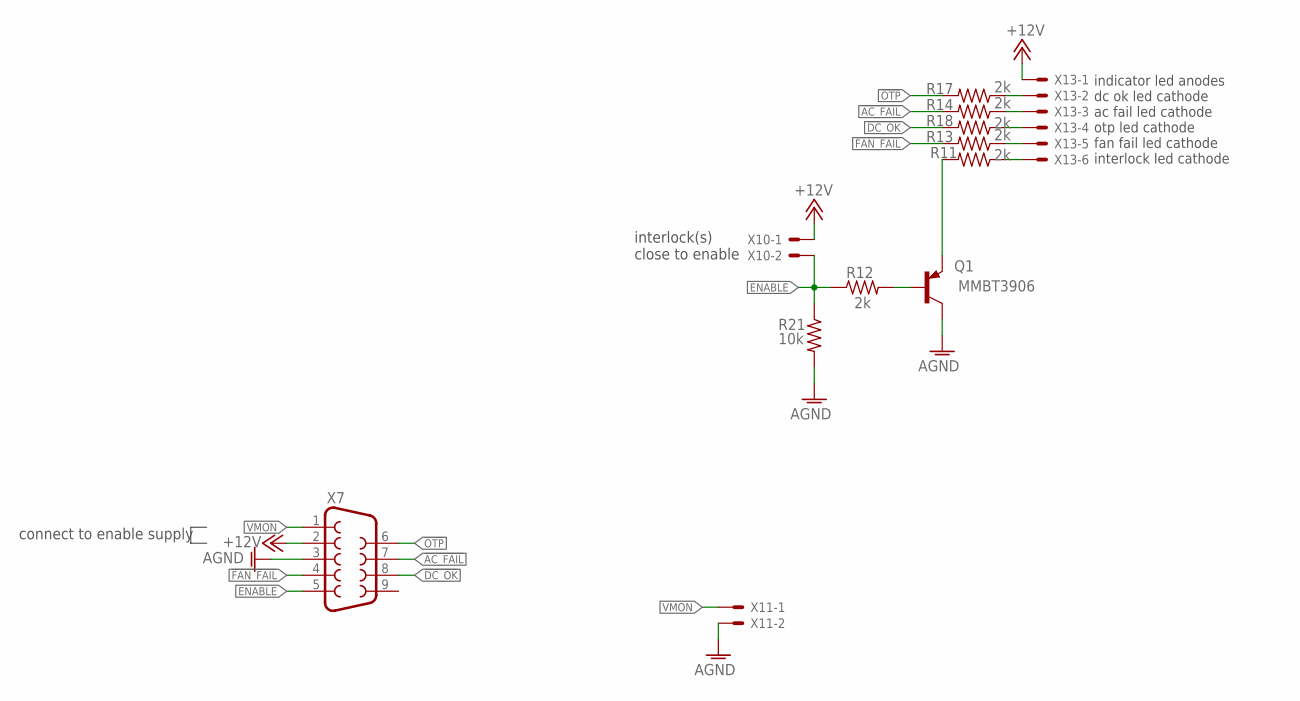
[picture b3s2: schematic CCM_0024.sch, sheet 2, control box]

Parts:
Q1: MMBT3906; SOT23-BEC
R11, R12, R13, R14, R17, R18: 2k; 0603
R21: 10k; 0603
X7: F09H
X10, X11: 22-23-2021
X13: 22-23-2061

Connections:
!AC_FAIL: R14.2, X7.7
!DC_OK: R18.2, X7.8
!FAN_FAIL: R13.2, X7.4
!OTP: R17.2, X7.6
+12V: X7.2, X10.1, X13.1
AGND: Q1.C, R21.2, X7.3, X11.2
ENABLE: R12.1, R21.1, X7.5, X10.2
unnamed: R11.1, X13.6
unnamed: Q1.E, R11.2
unnamed: R17.1, X13.2
unnamed: Q1.B, R12.2
unnamed: R14.1, X13.3
unnamed: R13.1, X13.5
unnamed: R18.1, X13.4
VMON: X7.1, X11.1

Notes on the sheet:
interlock(s) close to enable
connect to enable supply
indicator led anodes dc ok led cathode ac fail led cathode otp led cathode fan fail led cathode interlock led cathode
